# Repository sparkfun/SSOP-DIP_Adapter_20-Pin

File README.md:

SSOP DIP Adapter 20-Pin
=======================
[
*SparkFun SSOP20 to DIP Adapter (BOB-00499)*](https://www.sparkfun.com/products/499)

This pcb breaks out SSOP 20-pin packages to standard 0.1" headers. 

Repository Contents
-------------------
* **/Hardware** - All Eagle design files (.brd, .sch)

License Information
-------------------
The hardware is released under [Creative Commons ShareAlike 4.0 International](https://creativecommons.org/licenses/by-sa/4.0/).

Distributed as-is; no warranty is given.

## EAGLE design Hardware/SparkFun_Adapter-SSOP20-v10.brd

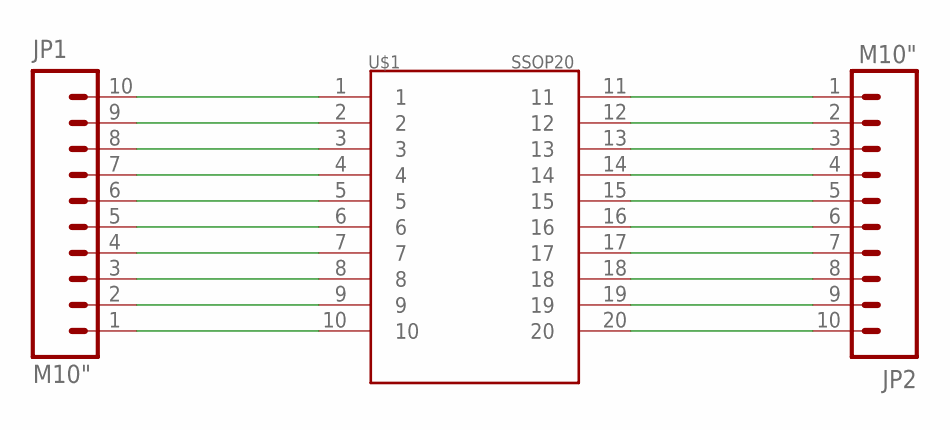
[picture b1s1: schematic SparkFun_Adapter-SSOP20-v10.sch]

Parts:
JP1, JP2: M10"; 1X10
U$1: SSOP20; SSOP20-LONG

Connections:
unnamed: JP1.10, U$1.1
unnamed: JP1.9, U$1.2
unnamed: JP1.7, U$1.4
unnamed: JP1.6, U$1.5
unnamed: JP1.3, U$1.8
unnamed: JP1.2, U$1.9
unnamed: JP1.1, U$1.10
unnamed: JP1.8, U$1.3
unnamed: JP1.5, U$1.6
unnamed: JP1.4, U$1.7
unnamed: JP2.1, U$1.11
unnamed: JP2.4, U$1.14
unnamed: JP2.6, U$1.16
unnamed: JP2.9, U$1.19
unnamed: JP2.10, U$1.20
unnamed: JP2.2, U$1.12
unnamed: JP2.3, U$1.13
unnamed: JP2.5, U$1.15
unnamed: JP2.7, U$1.17
unnamed: JP2.8, U$1.18

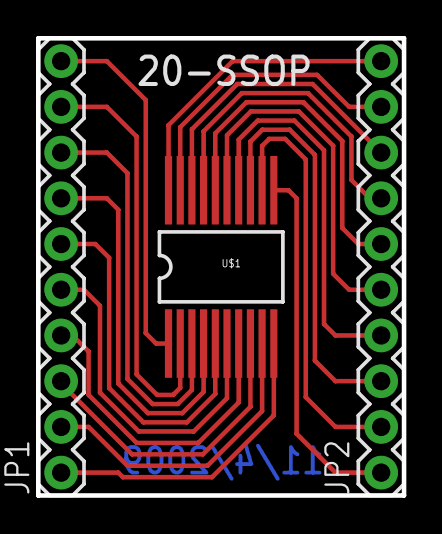
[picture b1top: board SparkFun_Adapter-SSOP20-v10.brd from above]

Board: 2 copper layers, 20.3 x 25.4 mm, 4 parts (1 on the bottom side), 20 nets.

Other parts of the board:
JP3: LOGO-SFENEW; SFE-NEW-WEBLOGO

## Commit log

2015-01-06 Initial hardware commit
